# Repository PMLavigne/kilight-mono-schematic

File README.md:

# KiLight Mono Schematic

The KiLight project is an open source / open hardware RGB+CCT wifi light controller system meant for use in filming environments that may be affected by the lower PWM frequencies and RF noise created by cheap off-the-shelf light controllers. KiLight is pronounced like "Key Light", get it. KiLight Mono is specifically the single-channel variant that can control a single RGB+CCT light - the project has been designed with an eye towards producing a dual-channel version as well, but that has not been built yet. 

This repository contains the circuit schematic and board layout files, if you want to build your own.

Made using [KiCad][KiCad] 8.0

[KiCad]: https://www.kicad.org/

## License

<p xmlns:cc="http://creativecommons.org/ns#" xmlns:dct="http://purl.org/dc/terms/"><a property="dct:title" rel="cc:attributionURL" href="https://github.com/PMLavigne/kilight-mono-schematic">KiLight Mono Schematics</a> by <a rel="cc:attributionURL dct:creator" property="cc:attributionName" href="https://github.com/PMLavigne">Patrick Lavigne</a> is licensed under <a href="https://creativecommons.org/licenses/by-nc-sa/4.0/?ref=chooser-v1" target="_blank" rel="license noopener noreferrer" style="display:inline-block;">CC BY-NC-SA 4.0</a></p>

This project makes use of the KiCad libraries, and may include cached copies of parts of them. The KiCad libraries are licensed under a modified Creative Commons CC-BY-SA 4.0 License, which you can read more about [here][KiCadLibraryLicense].

[KiCadLibraryLicense]: https://www.kicad.org/libraries/license/

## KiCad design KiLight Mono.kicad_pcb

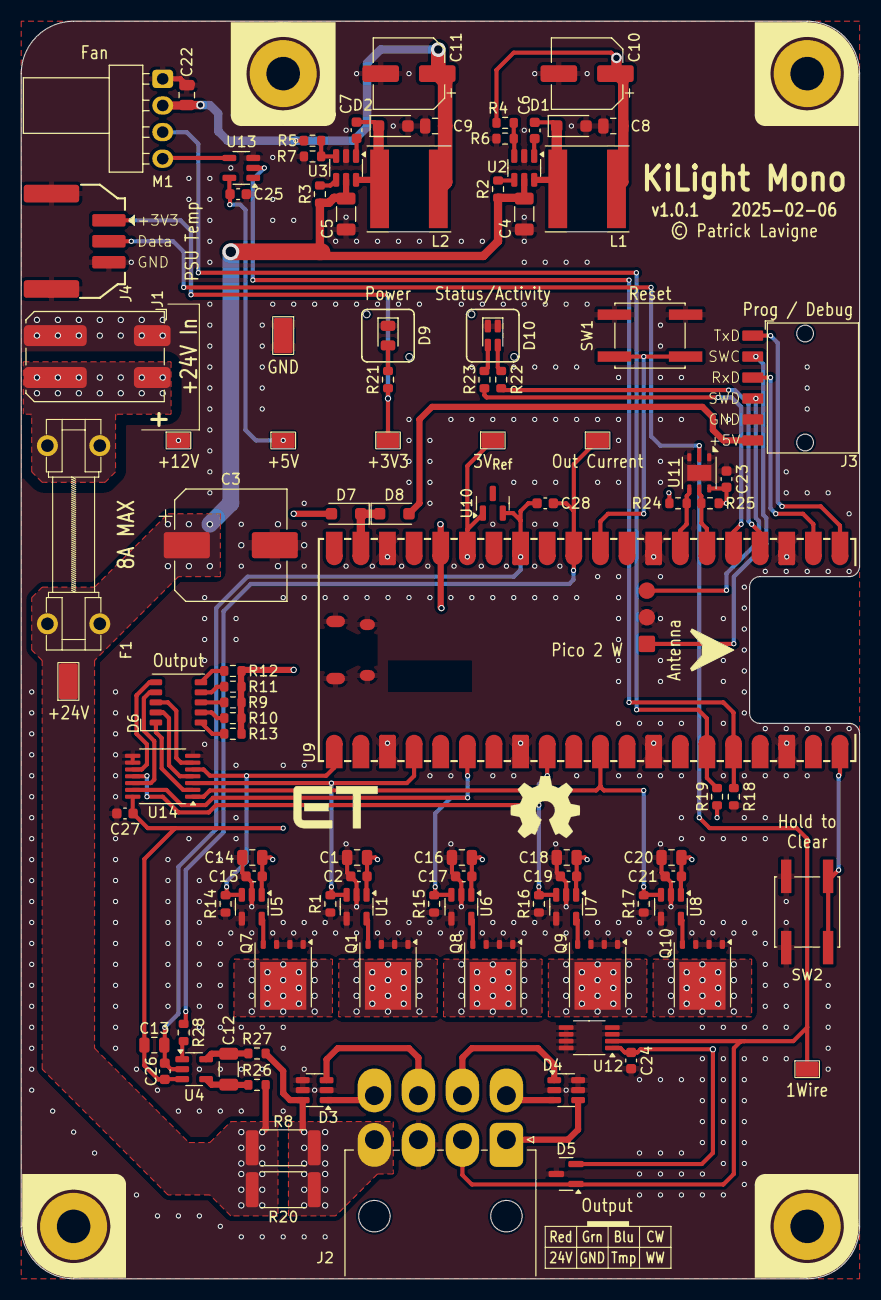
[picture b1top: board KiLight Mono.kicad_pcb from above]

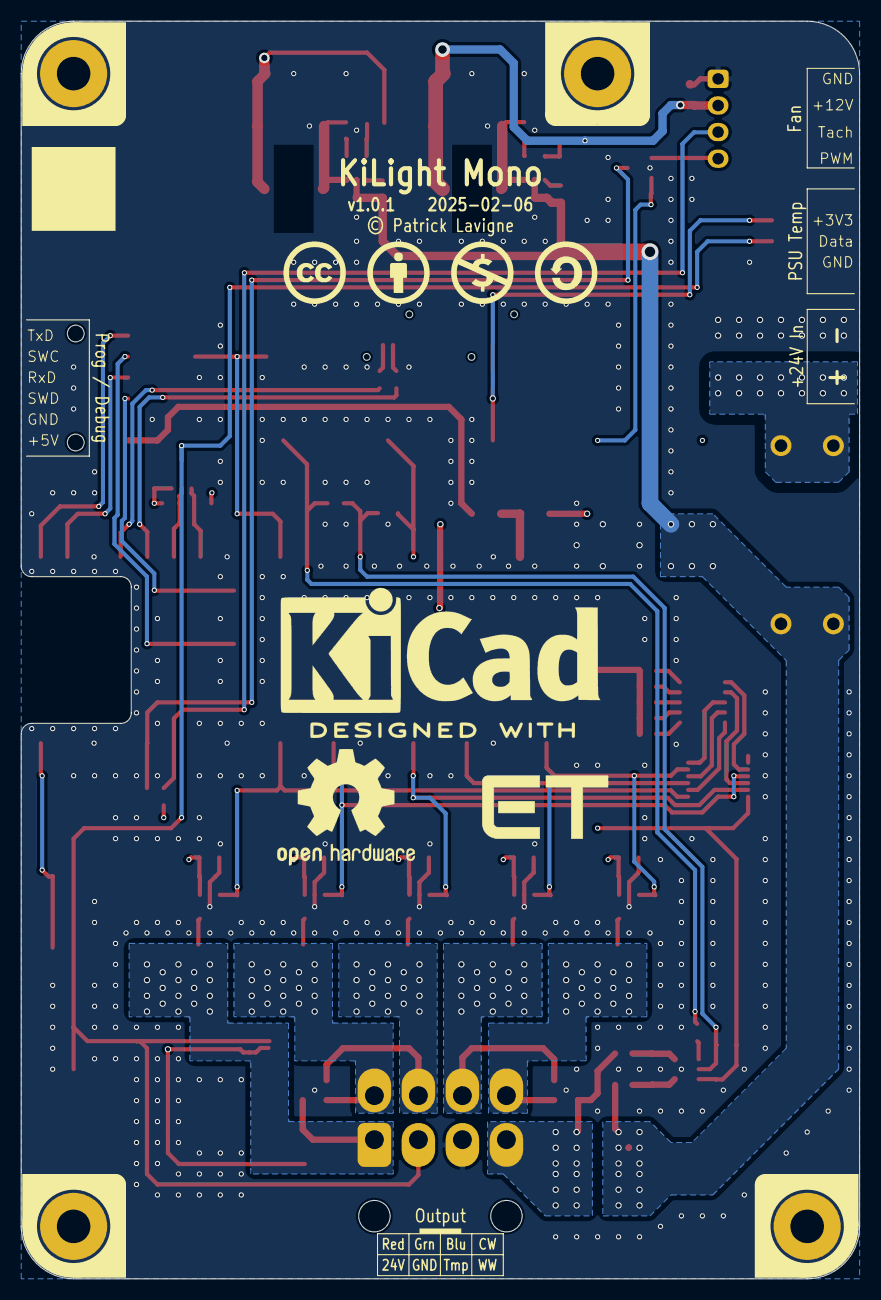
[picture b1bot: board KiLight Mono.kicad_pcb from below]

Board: 4 copper layers, 80.0 x 120.0 mm, 116 parts (7 on the bottom side), 65 nets.

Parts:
C1, C8, C9, C13, C14, C16, C18, C20, C22: 10uF; C_0805_2012Metric
C2, C6, C7, C15, C17, C19, C21, C23, C24, C25, C26, C27, C28: 100nF; C_0603_1608Metric
C3: 470uF; CP_Elec_10x12.5
C4, C5: 10uF; C_1206_3216Metric
C10: 100uF; CP_Elec_6.3x5.8
C11: 100uF; CP_Elec_6.3x7.7
C12: 100nF*; C_1206_3216Metric
D1, D2, D7, D8: PMEG2015EH; D_SOD-123F
D3, D4: SMS24T1G; SOT-23-6
D5: D1213A-01SO; SOT-23
D6: Output; LED_RGBCCT_5050-10
D9: Power; LED_LightPipe_Bivar-VLP_0805_2012Metric
D10: Status/Activity; LED_LightPipe_Bivar-VLP_BiColor_0805_2012Metric
F1: 8A; Fuseholder5x20_horiz_open_lateral_Type-II
H1: Hole A; MountingHole_3.2mm_M3_Pad
H2: Hole B; MountingHole_3.2mm_M3_Pad
H3: Hole C; MountingHole_3.2mm_M3_Pad
H4: Hole D; MountingHole_3.2mm_M3_Pad
ICN1: OSHW Front; OSHW-Symbol_6.7x6mm_SilkScreen
ICN2: OSHW Back; OSHW-Logo2_14.6x12mm_SilkScreen
ICN3: ET Front; Symbol_ET-Logo_8x4mm_SilkScreen
ICN4: ET Back; Symbol_ET-Logo_12x6mm_SilkScreen
ICN5: KiCad Back; KiCad-Logo2_12mm_SilkScreen
ICN6: CC Back; Symbol_CC_SilkScreenTop_6mm
ICN7: CC-BY Back; Symbol_CC_BY_SilkScreenTop_6mm
ICN8: CC-NC Back; Symbol_CC_NC_SilkScreenTop_6mm
ICN9: CC-SA Back; Symbol_CC_SA_SilkScreenTop_6mm
J1: +24V In; TerminalBlock_WAGO_2060-452_1x02_P4.00mm
J2: Output; Molex_Mini-Fit_Jr_45586-08_2x04_P4.20mm_Horizontal
J3: Prog / Debug; Amphenol_MiniTek_95000-x06_1x06_P2.0mm_Horizontal
J4: PSU Temp; Molex_DuraClik_502352-03XX_1x03-1MP-P2.00mm_SMD_Horizontal
L1: 33uH; L_Taiyo-Yuden_NR-80xx
L2: 47uH; L_Taiyo-Yuden_NR-80xx
M1: Fan; FanPinHeader_1x04_P2.54mm_THT_Horizontal
Q1, Q7, Q8, Q9, Q10: CSD18504Q5A; TDSON-8-1
R1, R2, R3, R14, R15, R16, R17, R18: 100K; R_0603_1608Metric
R4: 54.9K*; R_0603_1608Metric
R5: 147K*; R_0603_1608Metric
R6, R7, R28: 10K*; R_0603_1608Metric
R8, R20: 15m; R_2512_6332Metric
R9, R19: 2K; R_0603_1608Metric
R10, R11, R12, R13: 1K4; R_0603_1608Metric
R21, R22, R23: 1K; R_0603_1608Metric
R24, R25: 4K7; R_0603_1608Metric
R26, R27: 10*; R_0603_1608Metric
SW1: Reset; SW_SPST_EVQQ2
SW2: Hold to Clear; SW_SPST_EVQQ2
TP1: GND; TestPoint_Loop_1206_RCT_SMD
TP2: +3V3; TestPoint_Loop_0805_RCT_SMD
TP3: +5V; TestPoint_Loop_0805_RCT_SMD
TP4: +12V; TestPoint_Loop_0805_RCT_SMD
TP5: +24V; TestPoint_Loop_1206_RCT_SMD
TP6: Out Current; TestPoint_Loop_0805_RCT_SMD
TP7: 3V_{Ref}; TestPoint_Loop_0805_RCT_SMD
TP10: 1Wire; TestPoint_Loop_0805_RCT_SMD
U1, U5, U6, U7, U8: UCC27517A; SOT-23-5
U2, U3: LV2862; SOT-23-6
U4: INA281B2; SOT-23-5
U9: Pico 2 W; RPi_PicoW_SMD_NoTPs
U10: LM4040DBZ-3; SOT-23
U11: DS2485; Maxim_TDFN-6-1EP_3x3mm_P0.95mm_EP1.5x2.3mm
U12: TMP1826D; Texas_DGK0008A_VSSOP-8_3x3mm_P0.65mm
U13: 74AHCT1G04; SOT-23-5
U14: 74LVC06A; TSSOP-14_4.4x5mm_P0.65mm

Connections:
+3V3: C13.2, C23.2, C24.2, C26.2, C27.2, D5.2 (Vp), J4.1, R19.1, R21.1, R24.1, R25.1, TP2.1, U4.3 (V_{S}), U9.36 (3V3), U11.6 (V_{CC}), U12.1 (V_{DD}), U14.14 (V_{CC})
+5V: C8.1, C10.1, C25.2, D7.2 (A), L1.2, R4.2, R9.1, R10.1, R11.1, R12.1, R13.1, TP3.1, U13.5 (VCC)
+12V: C1.2, C2.2, C9.1, C11.1, C14.2, C15.2, C16.2, C17.2, C18.2, C19.2, C20.2, C21.2, C22.1, L2.2, M1.2 (+), R5.2, TP4.1, U1.1 (V_{DD}), U5.1 (V_{DD}), U6.1 (V_{DD}), U7.1 (V_{DD}), U8.1 (V_{DD})
+24V: C3.1, C4.1, C5.1, F1.2, R2.1, R3.1, R8.1, R20.1, R26.2, TP5.1, U2.5 (Vin), U3.5 (Vin)
/1Wire Data: D5.1 (CH1), J2.2, J4.2, TP10.1, U11.2 (IO), U12.2 (SDQ)
/Blue: R15.2, U6.3 (IN+), U9.6 (GPIO4), U14.13 (6A)
/CW: R16.2, U7.3 (IN+), U9.9 (GPIO6), U14.11 (5A)
/Controller/ADC V_{REF}: TP7.1, U9.35 (ADC_VREF), U10.1 (K)
/Controller/Activity LED: R22.1, U9.24 (GPIO18)
/Controller/Activity LED Anode: D10.1 (A1), R22.2
/Controller/Debug +5V: D8.2 (A), J3.6
/Controller/Debug RxD: J3.3, U9.22 (GPIO17)
/Controller/Debug TxD: J3.1, U9.21 (GPIO16)
/Controller/Fan PWM: R18.1, U9.16 (GPIO12), U13.2
/Controller/Fan Tacho: M1.3 (Tacho), R19.2, U9.15 (GPIO11)
/Controller/Fan-PWM-Out: M1.4 (PWM), U13.4
/Controller/Power LED Anode: D9.2 (A), R21.2
/Controller/SCL: R24.2, U9.27 (GPIO21), U11.4 (SCL)
/Controller/SDA: R25.2, U9.26 (GPIO20), U11.5 (SDA)
/Controller/SWCLK: J3.2, U9.D1 (SWCLK)
/Controller/SWDIO: J3.4, U9.D3 (SWDIO)
/Controller/Status LED: R23.1, U9.25 (GPIO19)
/Controller/Status LED Anode: D10.4 (A2), R23.2
/Controller/V_{SYS}: D7.1 (K), D8.1 (K), U9.39 (VSYS)
/Controller/~Clear: SW2.1, U9.20 (GPIO15)
/Controller/~RESET: SW1.1, U9.30 (RUN)
/Current: C28.1, R28.1, TP6.1, U9.31 (GPIO26_ADC0)
/Green: R1.2, U1.3 (IN+), U9.4 (GPIO2), U14.3 (2A)
/LED Drivers/+24V Out: D3.6 (Cathode), J2.4, R8.2, R20.2, R27.2
/LED Drivers/Blue Out: D4.1 (Cathode), J2.6, Q8.5 (D)
/LED Drivers/CW Out: D4.3 (Cathode), J2.5, Q9.5 (D)
/LED Drivers/Current Sense Amplifier/Filter +: C12.2, R26.1, U4.4 (IN+)
/LED Drivers/Current Sense Amplifier/Filter -: C12.1, R27.1, U4.5 (IN-)
/LED Drivers/Current Sense Amplifier/Out Current Raw: R28.2, U4.1 (OUT)
/LED Drivers/Green Out: D3.3 (Cathode), J2.7, Q1.5 (D)
/LED Drivers/LED Driver 1/Driver Gate: Q7.4 (G), U5.5 (OUT)
/LED Drivers/LED Driver 2/Driver Gate: Q1.4 (G), U1.5 (OUT)
/LED Drivers/LED Driver 3/Driver Gate: Q8.4 (G), U6.5 (OUT)
/LED Drivers/LED Driver 4/Driver Gate: Q9.4 (G), U7.5 (OUT)
/LED Drivers/LED Driver 5/Driver Gate: Q10.4 (G), U8.5 (OUT)
/LED Drivers/Output Indicator/Blue Anode: D6.9 (BA), R11.2
/LED Drivers/Output Indicator/Blue Cathode: D6.2 (BK), U14.12 (6Y)
/LED Drivers/Output Indicator/CW Anode: D6.10 (CWA), R12.2
/LED Drivers/Output Indicator/CW Cathode: D6.1 (CWK), U14.10 (5Y)
/LED Drivers/Output Indicator/Green Anode: D6.7 (GA), R10.2
/LED Drivers/Output Indicator/Green Cathode: D6.4 (GK), U14.4 (2Y)
/LED Drivers/Output Indicator/Red Anode: D6.8 (RA), R9.2
/LED Drivers/Output Indicator/Red Cathode: D6.3 (RK), U14.6 (3Y)
/LED Drivers/Output Indicator/WW Anode: D6.6 (WWA), R13.2
/LED Drivers/Output Indicator/WW Cathode: D6.5 (WWK), U14.2 (1Y)
/LED Drivers/Red Out: D3.1 (Cathode), J2.8, Q7.5 (D)
/LED Drivers/WW Out: D4.4 (Cathode), J2.1, Q10.5 (D)
/Power Supply/+24V Raw: F1.1, J1.2
/Power Supply/Voltage Rails/5V Buck Boot: C6.1, U2.1 (CB)
/Power Supply/Voltage Rails/5V Buck Feedback: R4.1, R6.1, U2.3 (FB)
/Power Supply/Voltage Rails/5V Buck Switch: C6.2, D1.1 (K), L1.1, U2.6 (SW)
/Power Supply/Voltage Rails/5V Enable: R2.2, U2.4 (~SHDN)
/Power Supply/Voltage Rails/12V Buck Boot: C7.1, U3.1 (CB)
/Power Supply/Voltage Rails/12V Buck Feedback: R5.1, R7.2, U3.3 (FB)
/Power Supply/Voltage Rails/12V Buck Switch: C7.2, D2.1 (K), L2.1, U3.6 (SW)
/Power Supply/Voltage Rails/12V Enable: R3.2, U3.4 (~SHDN)
/Red: R14.2, U5.3 (IN+), U9.1 (GPIO0), U14.5 (3A)
/WW: R17.2, U8.3 (IN+), U9.11 (GPIO8), U14.1 (1A)
GND: C1.1, C2.1, C3.2, C4.2, C5.2, C8.2, C9.2, C10.2, C11.2, C14.1, C15.1, C16.1, C17.1, C18.1, C19.1, C20.1, C21.1, C22.2, C23.1, C24.1, C25.1, C27.1, D1.2 (A), D2.2 (A), D3.2 (CommonAnode), D3.4 (Cathode), D3.5 (CommonAnode), D4.2 (CommonAnode), D4.5 (CommonAnode), D4.6 (Cathode), D5.3 (Vn), D9.1 (K), D10.2 (K1), D10.3 (K2), H1.1, H2.1, H3.1, H4.1, J1.1, J2.3, J3.5, J4.3, J4.MP (MountPin), M1.1 (-), Q1.1 (S), Q1.2 (S), Q1.3 (S), Q7.1 (S), Q7.2 (S), Q7.3 (S), Q8.1 (S), Q8.2 (S), Q8.3 (S), Q9.1 (S), Q9.2 (S), Q9.3 (S), Q10.1 (S), Q10.2 (S), Q10.3 (S), R1.1, R6.2, R7.1, R14.1, R15.1, R16.1, R17.1, R18.2, SW1.2, SW2.2, TP1.1, U1.2 (GND), U1.4 (IN-), U2.2 (GND), U3.2 (GND), U5.2 (GND), U5.4 (IN-), U6.2 (GND), U6.4 (IN-), U7.2 (GND), U7.4 (IN-), U8.2 (GND), U8.4 (IN-), U9.3 (GND), U9.8 (GND), U9.13 (GND), U9.18 (GND), U9.23 (GND), U9.28 (GND), U9.38 (GND), U9.D2 (GND), U9.MP (USB_Shield), U11.1 (GPIO), U11.3 (GND), U11.7 (GND), U12.3 (ADDR), U12.4 (GND), U12.5 (IO3), U12.6 (IO0), U12.7 (IO1), U12.8 (IO2), U13.3 (GND), U14.7 (GND), U14.8 (4Y), U14.9 (4A)
GNDA: C13.1, C26.1, C28.2, U4.2 (GND), U9.33 (AGND), U10.2 (A)

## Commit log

2025-02-07 Fix README Links
    - Apparently I forgot how markdown links work. Fixed.

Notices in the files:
KiLight Mono.kicad_pcb:
© Patrick Lavigne
